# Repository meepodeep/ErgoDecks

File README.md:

# ErgoDecks not ErgoDOX
- ## Featuring
  - ### Two independent Bluetooth halves.
  - ### 3d printed case
  - ### Custom PCB
  - ### Kalih Choc switch compatibility.

**BOM**

| Item |Quantity |Total price+Shipping|Use in project|Item source|
| ------------- | ------------- | ------------- | ------------- | ------------- |
| Pcb  | 5x (minimum order) |$32.05|Mount Everything to this| JLCPCB |
| NRF52840	  | 2x |$10.77|Drive the boards|[Aliexpress](https://www.aliexpress.us/item/3256807018711621.html?spm=a2g0o.productlist.main.1.5a6eie0Hie0H9D&aem_p4p_detail=202505281428561705173893544160001721434&algo_pvid=e8c677b1-5ee7-4a06-9cf3-86530aadc628&algo_exp_id=e8c677b1-5ee7-4a06-9cf3-86530aadc628-0&pdp_ext_f=%7B%22order%22%3A%22307%22%2C%22eval%22%3A%221%22%7D&pdp_npi=4%40dis%21USD%214.39%214.39%21%21%2131.45%2131.45%21%402101c71a17484677363603280ed1bd%2112000039797470328%21sea%21US%214381910819%21X&curPageLogUid=OhOCTEVGrX7q&utparam-url=scene%3Asearch%7Cquery_from%3A&search_p4p_id=202505281428561705173893544160001721434_1)|
|Kalih Choc 10pc	|4x|$31.00|Be switches|[Little Keyboards](https://www.littlekeyboards.com/collections/keyboard-switches/products/kailh-choc-low-profile-switches)|
|Filament of your choice|an amount|0$|make the case|wherever you buy filament ( I have this)|
|301230 lithium battery|2x|$8.76|Power The boards|[Aliexpress](https://www.aliexpress.us/item/3256806602655947.html?spm=a2g0o.productlist.main.3.1f175238MrCTZJ&algo_pvid=eaa25171-69cd-4b4e-b96e-f3d39bffa79c&algo_exp_id=eaa25171-69cd-4b4e-b96e-f3d39bffa79c-2&pdp_ext_f=%7B%22order%22%3A%2274%22%2C%22eval%22%3A%221%22%7D&pdp_npi=4%40dis%21USD%218.10%214.70%21%21%2157.98%2133.63%21%402103205117484706855838784ee72d%2112000038305675270%21sea%21US%214381910819%21X&curPageLogUid=6xafRV7sUtxr&utparam-url=scene%3Asearch%7Cquery_from%3A)|
|1N4148 Diodes 100pc|1x|$9.26|be diodes|[Aliexpress](https://www.aliexpress.us/item/3256806058794623.html?spm=a2g0o.productlist.main.2.76fa3771JY9hHq&algo_pvid=3d141e2c-c612-4dda-8ee7-d81e18ab9714&algo_exp_id=3d141e2c-c612-4dda-8ee7-d81e18ab9714-1&pdp_ext_f=%7B%22order%22%3A%22914%22%2C%22eval%22%3A%221%22%7D&pdp_npi=4%40dis%21USD%211.84%211.28%21%21%2113.14%219.15%21%402101c80217484699707521224ee30c%2112000036448323916%21sea%21US%214381910819%21X&curPageLogUid=FxGJkqmD4E5N&utparam-url=scene%3Asearch%7Cquery_from%3A)|
|Keycaps 1u 10pc|x4|$21.11|be keycaps|[adafruit](https://www.adafruit.com/product/5737)|
|Keycaps 1.5u 2pc|x2|$4.66|be keycaps|[Aliexpress](https://www.aliexpress.us/item/3256805730011012.html?spm=a2g0o.productlist.main.8.4ba31a67KZIfyi&algo_pvid=95a4ad10-6234-413b-ba30-70ed94a3c48a&algo_exp_id=95a4ad10-6234-413b-ba30-70ed94a3c48a-7&pdp_ext_f=%7B%22order%22%3A%2263%22%2C%22eval%22%3A%221%22%7D&pdp_npi=4%40dis%21USD%212.33%212.33%21%21%212.33%212.33%21%40210337bc17484682352145208eab6e%2112000034838215571%21sea%21US%214381910819%21X&curPageLogUid=KAtk70CozSZd&utparam-url=scene%3Asearch%7Cquery_from%3A)|
|Everything||$105.62|||

## **Download Gerbers.zip for the gerbers and ErgoDecksVx.3mf/.step/.f3z for the case!**
- ## **Assembly**
  - Solder diodes onto the PCB.
  - Solder switches onto the PCB.
  - Solder microcontrollers onto the pcb.
  - Solder the battery to the bat terminals on the mcu.
  - Attach the battery using double sided tape to the bottom half of the case in the battery area.
  - 
  - Use m3 bolts to secure the pcb and top case to the bottom half of the case.

- ## **Software**
  - download the firmware.zip file and flash the left file to the left half and the right file to the right half by dragging and dropping it into the virtual disk on the MCUs in bootloader mode.

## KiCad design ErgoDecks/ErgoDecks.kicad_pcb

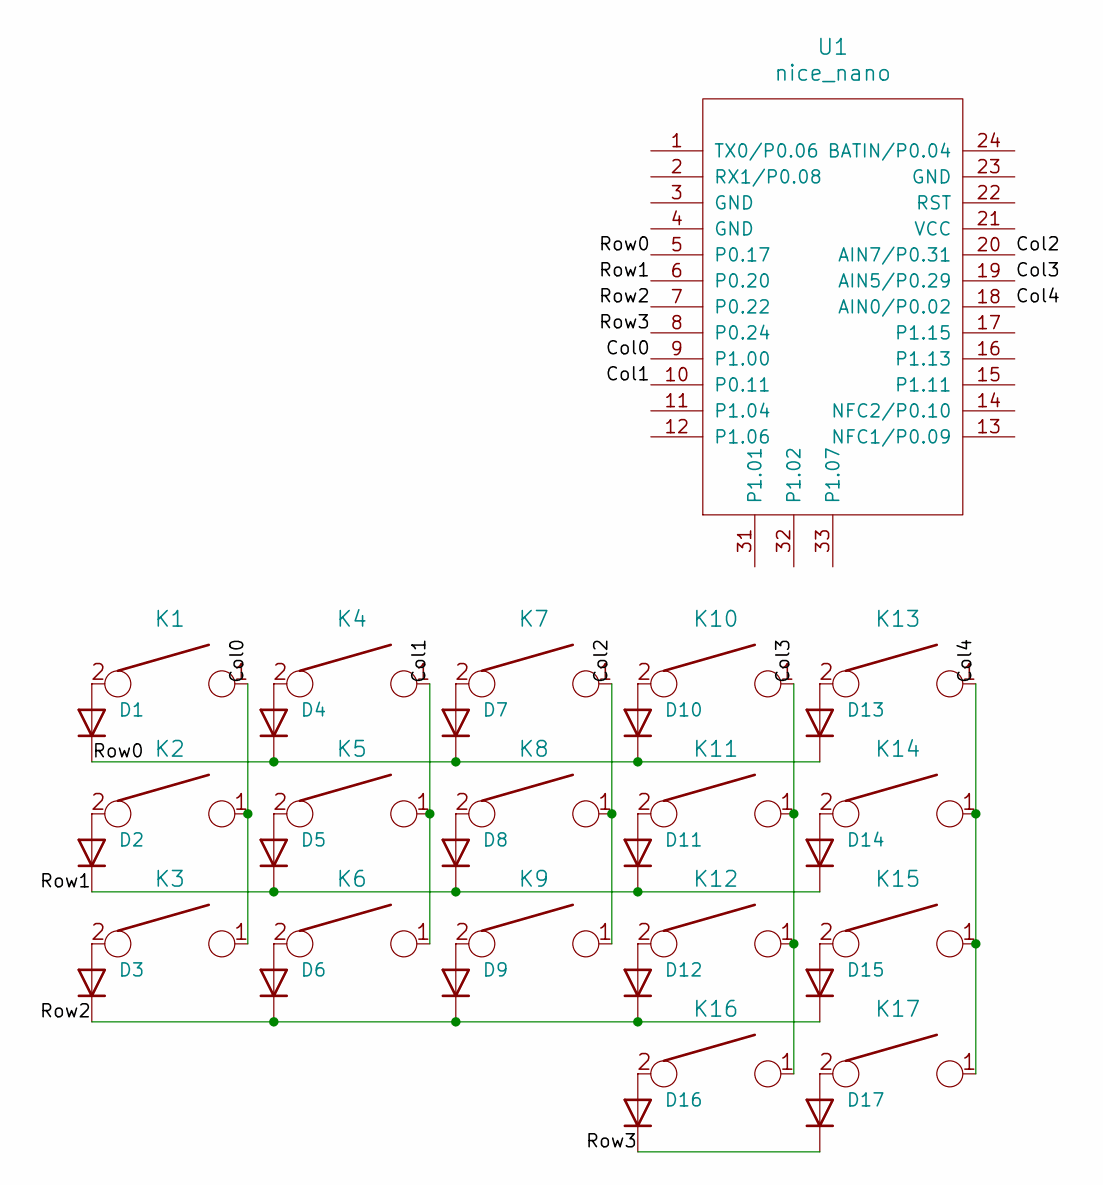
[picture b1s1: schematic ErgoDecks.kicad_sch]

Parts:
D1, D2, D3, D4, D5, D6, D7, D8, D9, D10, D11, D12, D13, D14, D15, D16, D17: D_SOD123_axial
K1, K2, K3, K4, K5, K6, K7, K8, K9, K10, K11, K12, K13, K14, K15, K16, K17: KEYSW; SW_PG1350_reversible
U1: nice_nano

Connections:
/Col0: K1.1, K2.1, K3.1, U1.9 (P1.00)
/Col1: K4.1, K5.1, K6.1, U1.10 (P0.11)
/Col2: K7.1, K8.1, K9.1, U1.20 (AIN7/P0.31)
/Col3: K10.1, K11.1, K12.1, K16.1, U1.19 (AIN5/P0.29)
/Col4: K13.1, K14.1, K15.1, K17.1, U1.18 (AIN0/P0.02)
/Row0: D1.1 (K), D4.1 (K), D7.1 (K), D10.1 (K), D13.1 (K), U1.5 (P0.17)
/Row1: D2.1 (K), D5.1 (K), D8.1 (K), D11.1 (K), D14.1 (K), U1.6 (P0.20)
/Row2: D3.1 (K), D6.1 (K), D9.1 (K), D12.1 (K), D15.1 (K), U1.7 (P0.22)
/Row3: D16.1 (K), D17.1 (K), U1.8 (P0.24)
unnamed: D1.2 (A), K1.2
unnamed: D2.2 (A), K2.2
unnamed: D3.2 (A), K3.2
unnamed: D4.2 (A), K4.2
unnamed: D5.2 (A), K5.2
unnamed: D6.2 (A), K6.2
unnamed: D7.2 (A), K7.2
unnamed: D8.2 (A), K8.2
unnamed: D9.2 (A), K9.2
unnamed: D10.2 (A), K10.2
unnamed: D11.2 (A), K11.2
unnamed: D12.2 (A), K12.2
unnamed: D13.2 (A), K13.2
unnamed: D14.2 (A), K14.2
unnamed: D15.2 (A), K15.2
unnamed: D16.2 (A), K16.2
unnamed: D17.2 (A), K17.2

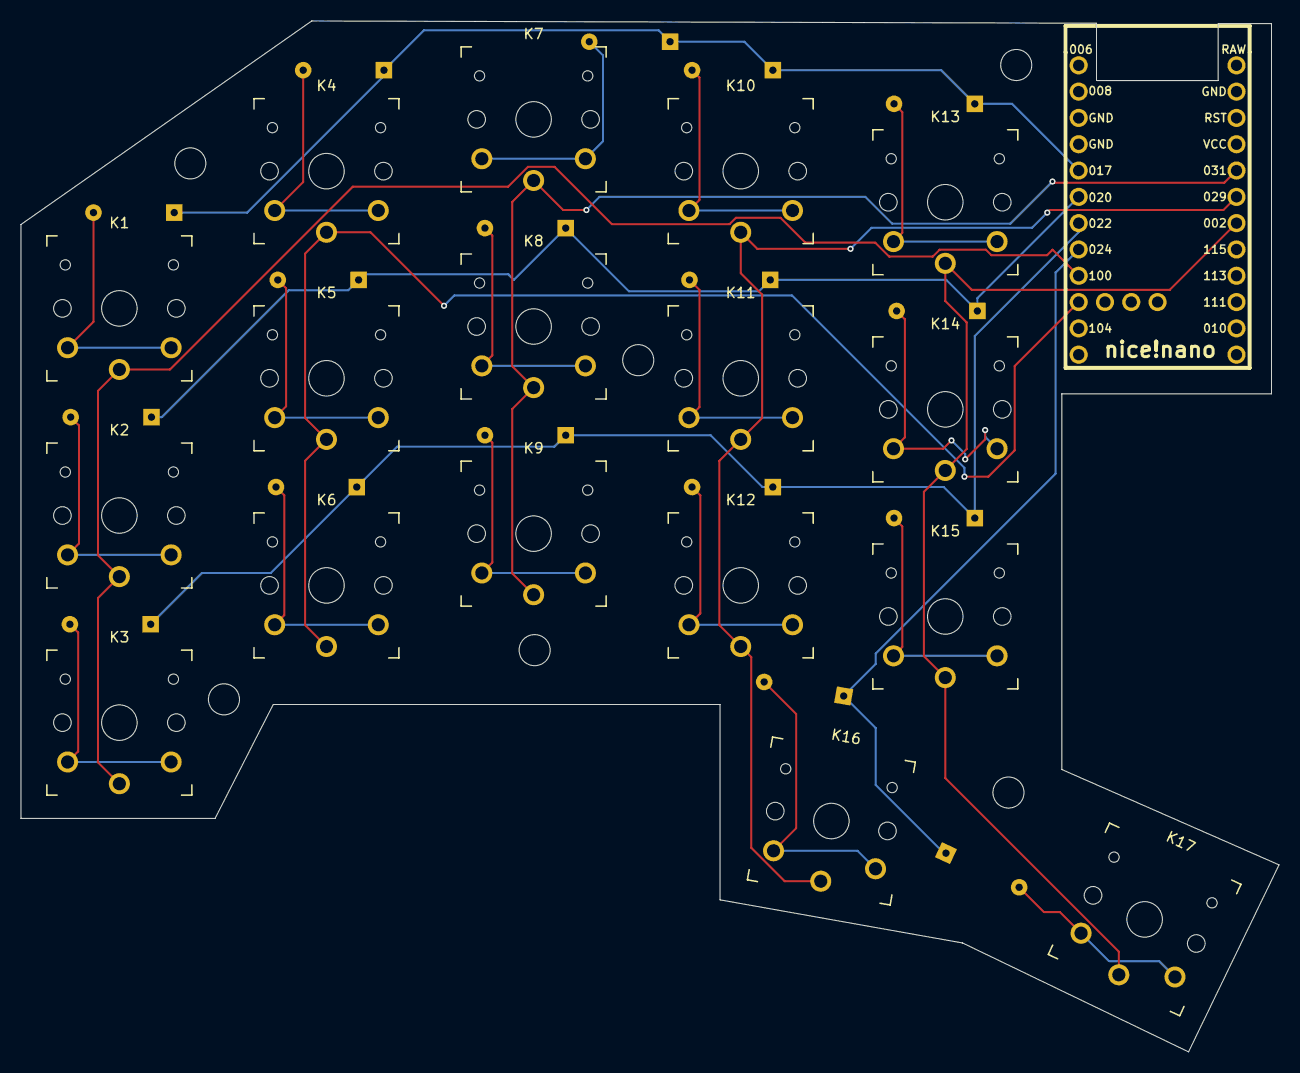
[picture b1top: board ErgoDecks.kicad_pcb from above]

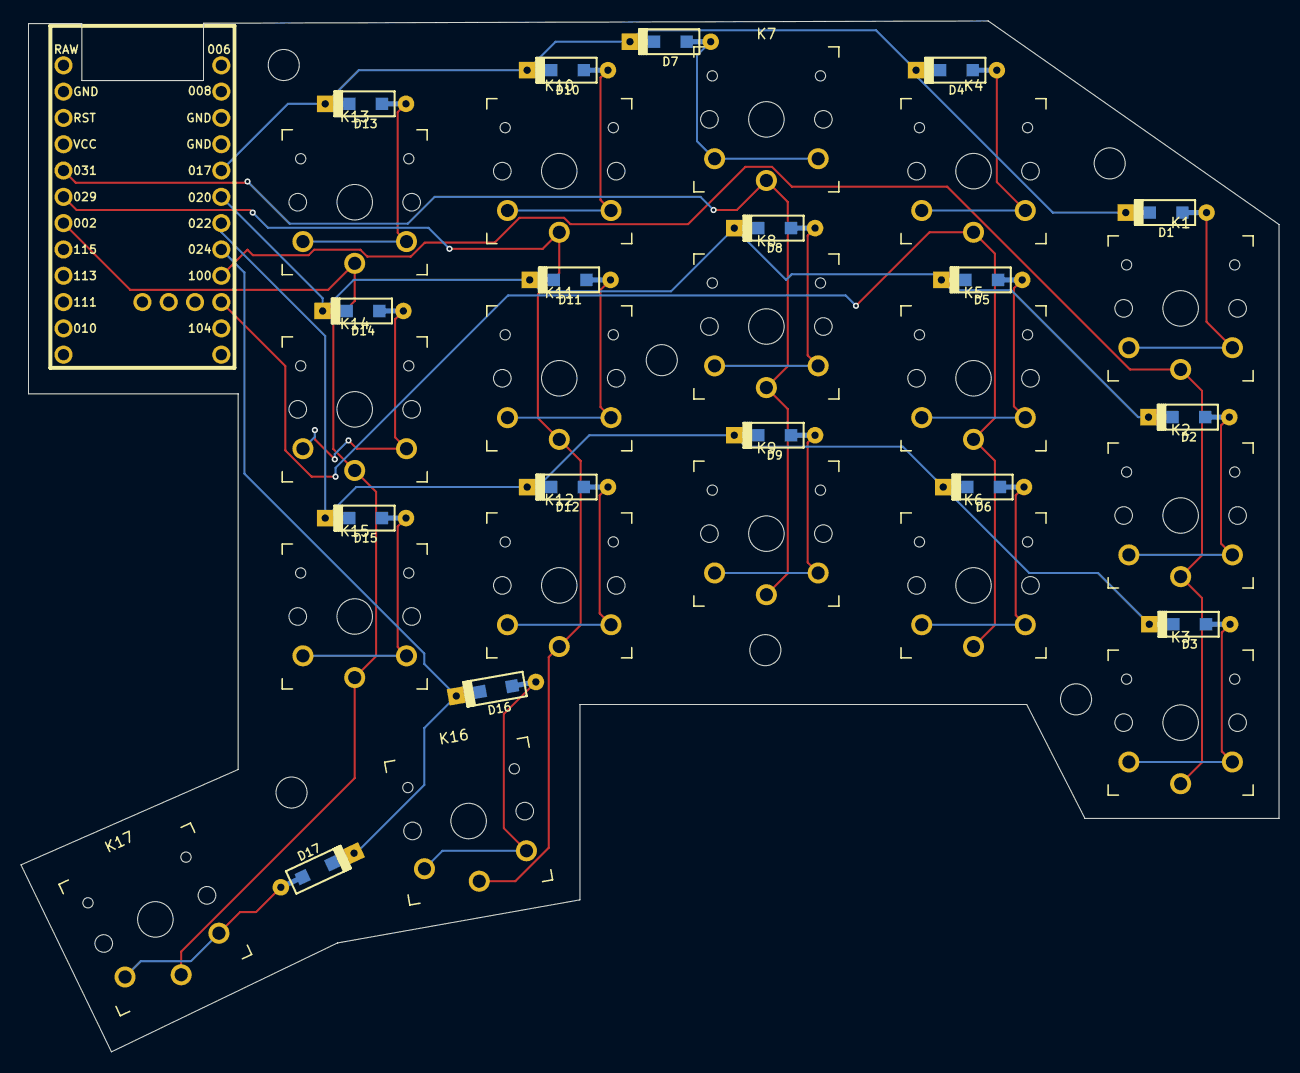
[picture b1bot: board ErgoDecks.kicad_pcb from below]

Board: 2 copper layers, 121.5 x 99.5 mm, 35 parts (17 on the bottom side), 26 nets.
